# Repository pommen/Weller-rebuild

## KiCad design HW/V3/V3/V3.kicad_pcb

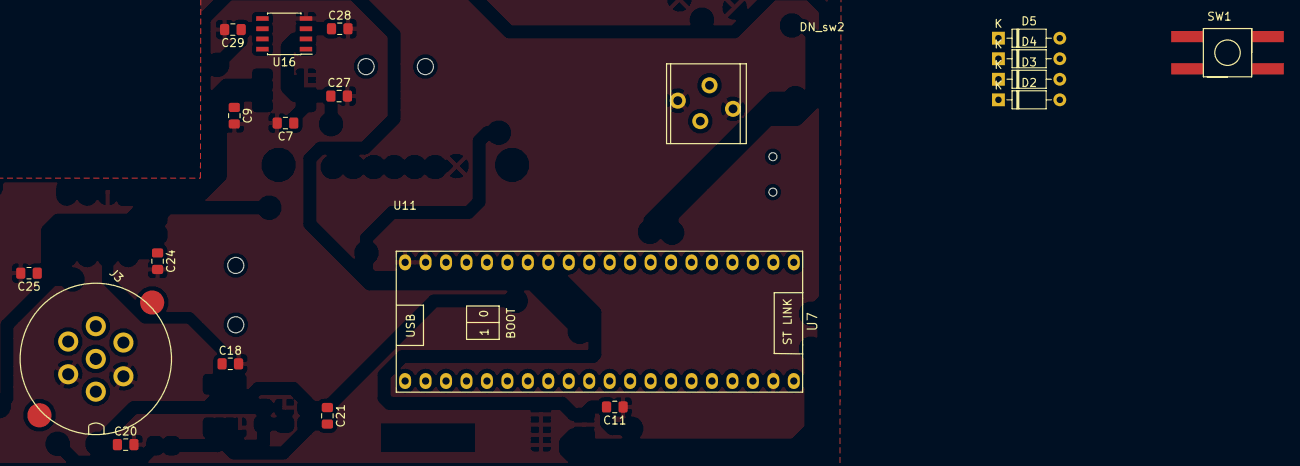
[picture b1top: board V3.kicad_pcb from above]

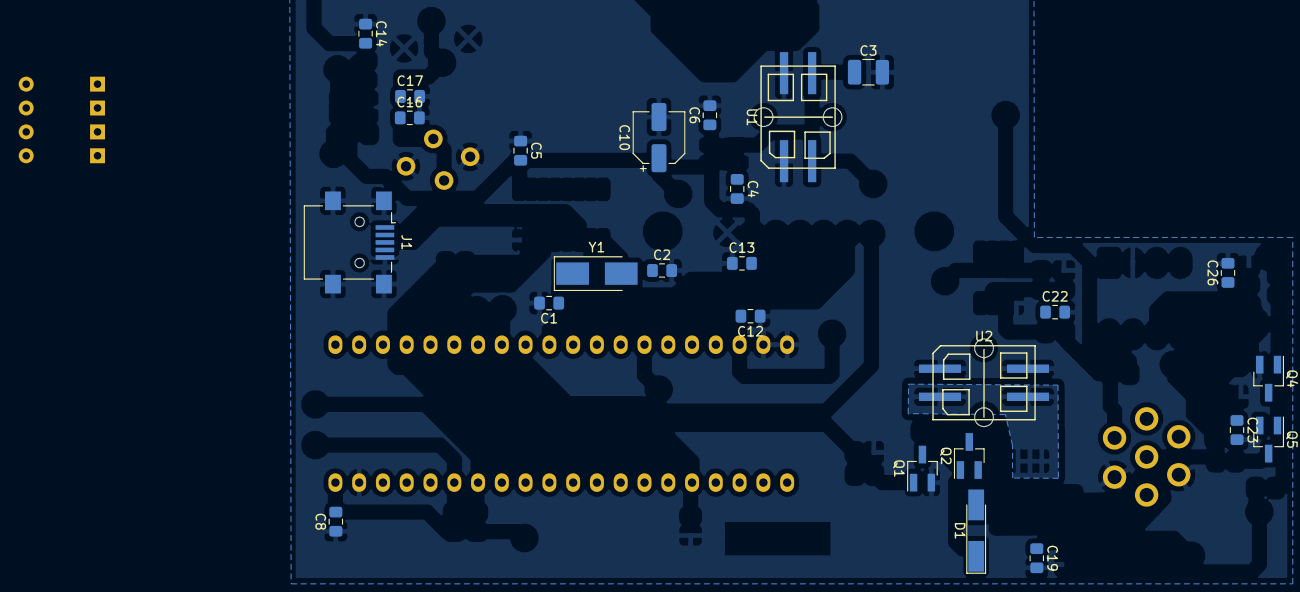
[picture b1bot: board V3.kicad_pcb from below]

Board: 2 copper layers, 47 parts (26 on the bottom side), 17 nets, no tracks yet.

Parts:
C1, C2: C_Small; C_0805_2012Metric_Pad1.15x1.40mm_HandSolder
C3: 68uf; C_1210_3225Metric_Pad1.42x2.65mm_HandSolder
C4: 1u; C_0805_2012Metric_Pad1.15x1.40mm_HandSolder
C5, C7, C8, C9, C11, C12, C13, C14, C18, C19, C20, C25: 100n; C_0805_2012Metric_Pad1.15x1.40mm_HandSolder
C6: 100pf; C_0805_2012Metric_Pad1.15x1.40mm_HandSolder
C10: 10uF; CP_Elec_5x5.3
C16, C17, C22, C23, C24, C26: 10n; C_0805_2012Metric_Pad1.15x1.40mm_HandSolder
C21: 1n; C_0805_2012Metric_Pad1.15x1.40mm_HandSolder
C27, C28, C29: 2.2uF; C_0805_2012Metric_Pad1.15x1.40mm_HandSolder
D1: 1N4148; D_MiniMELF_Handsoldering
D2, D3, D4, D5: 1N4148; D_DO-35_SOD27_P7.62mm_Horizontal
DN_sw2: SW_Push_Dual; WellerBTN
J1: USB_B_Mini; USB_Mini-B_Lumberg_2486_01_Horizontal
J3: WellerConn
Q1, Q2, Q4: BSS138; SOT-23_Handsoldering
Q5: A03401; SOT-23_Handsoldering
SW1: SW_Push; PushBTN KSC241G
U1: +7.5V; Conn_Microfit_Vertical_molex
U2: +24; Conn_Microfit_Vertical_molex
U7: Bluepill
U11: OLED_128x64_SPI_0.96; OLED_128x64_i2c
U16: MAX6241; SOIC-8_3.9x4.9mm_P1.27mm
Y1: 12MHZ; Crystal_SMD_5032-2Pin_5.0x3.2mm_HandSoldering

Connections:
+3V3: C5.2, C8.2, C10.1, C11.2, C12.2, C13.2, C14.2, U7.18, U7.40
+4V: C29.1, U16.6
+5V: C9.1, C18.1, C20.1, C25.1, D2.1, D4.1, Q5.2
+7.5V: C3.1, C4.1, C27.1, U1.2, U1.3, U16.2
+24V: Q2.3, U2.2, U2.3
/MOSFETCurr: C21.1, U7.14
GND: C1.2, C2.2, C3.2, C4.2, C5.1, C6.2, C7.2, C8.1, C9.2, C10.2, C11.1, C12.1, C13.1, C14.1, C16.2, C17.2, C18.2, C19.2, C20.2, C22.2, C23.2, C24.2, C25.2, C26.2, C27.2, C28.2, C29.2, D3.2, D5.2, DN_sw2.2, DN_sw2.4, J1.5, J1.6, J3.1, J3.5, Q1.2, Q4.2, SW1.2, U1.1, U1.4, U2.1, U2.4, U7.19, U7.20, U7.39, U16.4
unnamed: C1.1, Y1.1
unnamed: C2.1, Y1.2
unnamed: C16.1, DN_sw2.1, DN_sw2.3
unnamed: C22.1, D2.2, D3.1
unnamed: C23.1, D4.2, D5.1
unnamed: C28.1, U16.3
unnamed: D1.1, Q1.3, Q2.1
unnamed: D1.2, Q2.2
unnamed: Q4.3, Q5.1
unnamed: SW1.1, U7.17

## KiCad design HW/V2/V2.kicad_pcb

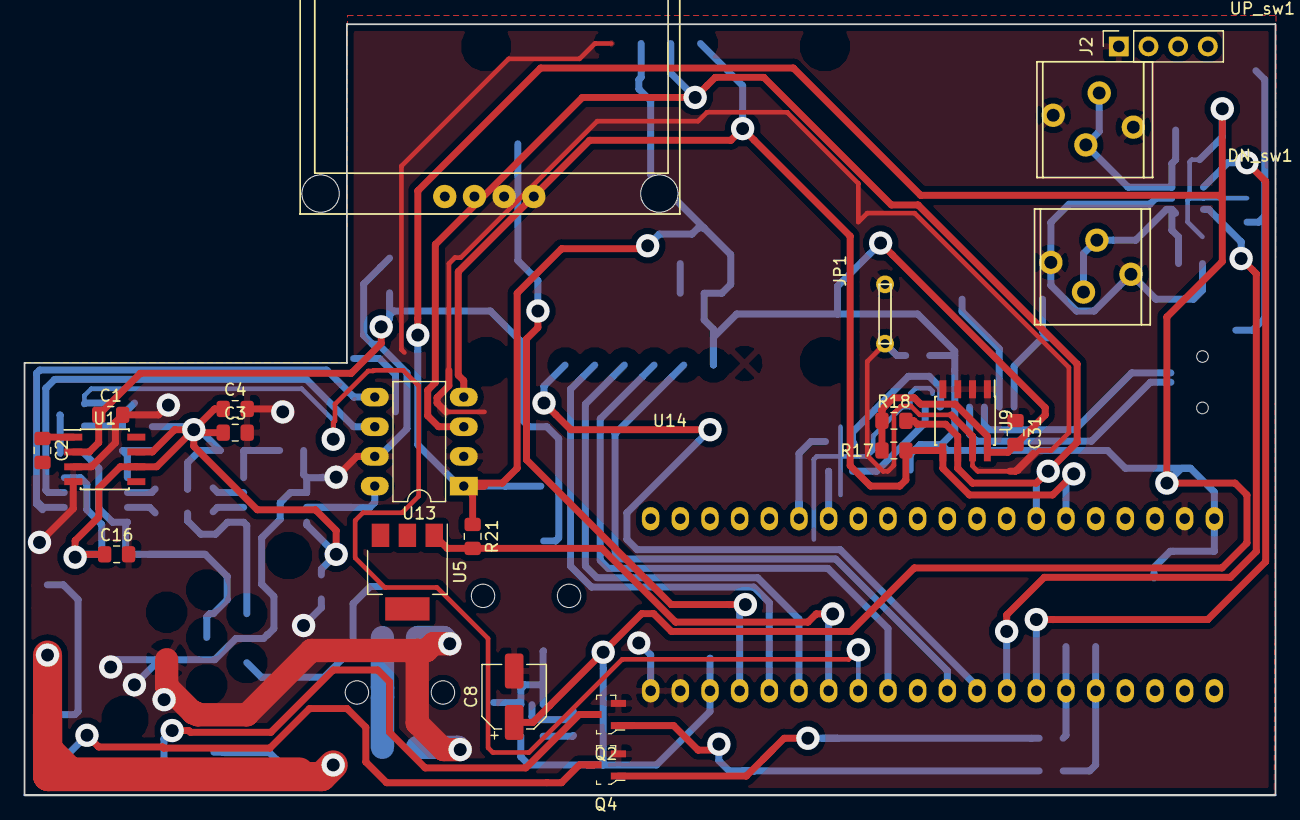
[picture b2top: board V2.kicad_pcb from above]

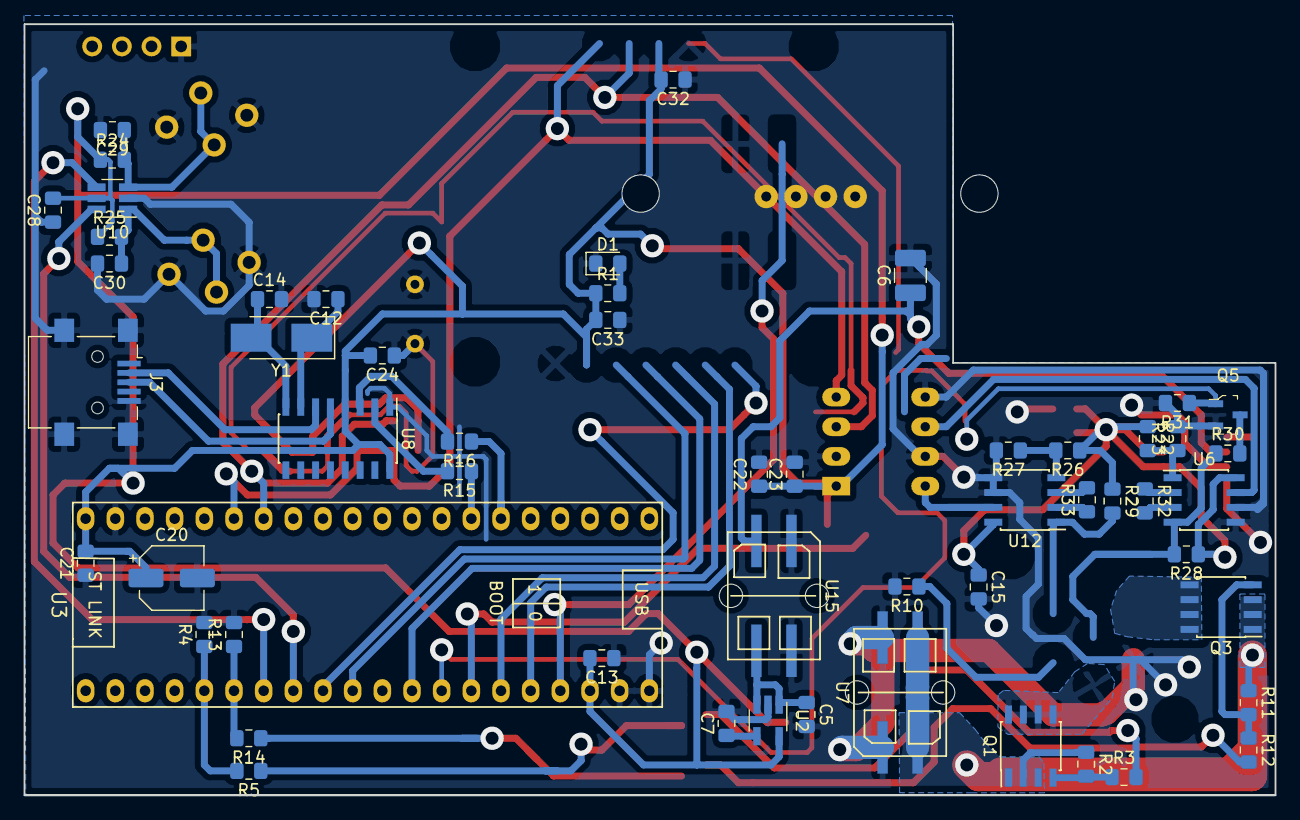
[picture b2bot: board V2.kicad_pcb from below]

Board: 2 copper layers, 107.1 x 66.0 mm, 76 parts (55 on the bottom side), 46 nets.

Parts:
C1, C2, C3: 100N; C_0805_2012Metric_Pad1.15x1.40mm_HandSolder
C4: 1u; C_0805_2012Metric_Pad1.15x1.40mm_HandSolder
C5: 1uF; C_0805_2012Metric_Pad1.15x1.40mm_HandSolder
C6: 68uf; C_1210_3225Metric_Pad1.42x2.65mm_HandSolder
C7: 100pF; C_0805_2012Metric_Pad1.15x1.40mm_HandSolder
C8: 2.2uF; CP_Elec_5x5.3
C12, C14: C_Small; C_0805_2012Metric_Pad1.15x1.40mm_HandSolder
C13, C15, C16, C21, C22, C24, C28, C31, C32, C33: 100n; C_0805_2012Metric_Pad1.15x1.40mm_HandSolder
C20: 10uF; CP_Elec_5x5.3
C23, C29, C30: 10n; C_0805_2012Metric_Pad1.15x1.40mm_HandSolder
D1: Green; D_0805_2012Metric_Pad1.15x1.40mm_HandSolder
DN_sw1: SW_Push_Dual; WellerBTN
J2: I2CHeader; PinSocket_1x04_P2.54mm_Vertical
J3: USB_B_Mini; USB_Mini-B_Lumberg_2486_01_Horizontal
JP1: Grounding pad; JUMPER_5MM
Q1, Q3: Si4435; SOIC-8_3.9x4.9mm_P1.27mm
Q2, Q4, Q5: BSS138; SOT-23-3
R1, R2, R3, R11, R12, R31: 10K; R_0805_2012Metric_Pad1.15x1.40mm_HandSolder
R4, R13, R24, R25: 100K; R_0805_2012Metric_Pad1.15x1.40mm_HandSolder
R5, R14: 100R; R_0805_2012Metric_Pad1.15x1.40mm_HandSolder
R10: 1M; R_0805_2012Metric_Pad1.15x1.40mm_HandSolder
R15, R16: 1k; R_0805_2012Metric_Pad1.15x1.40mm_HandSolder
R17, R18: 5k1; R_0805_2012Metric_Pad1.15x1.40mm_HandSolder
R21: 1K5-5K; R_0805_2012Metric_Pad1.15x1.40mm_HandSolder
R22, R23, R26, R27, R28, R29: 1K; R_0805_2012Metric_Pad1.15x1.40mm_HandSolder
R30: 2K; R_0805_2012Metric_Pad1.15x1.40mm_HandSolder
R32, R33: 5.62K 1%; R_0805_2012Metric_Pad1.15x1.40mm_HandSolder
U1: MAX6126_50; SOIC-8_3.9x4.9mm_P1.27mm
U2: AP2210-3.3V; SOT-23-5_HandSoldering
U3: Bluepill
U5: DS2401Z; SOT-223
U6, U12: AD8221; SOIC-8_3.9x4.9mm_P1.27mm
U7: +24VDC; Conn_Microfit_Vertical_molex
U8: CH340G; SOIC-16_3.9x9.9mm_P1.27mm
U9: M24C01-WMN; SOIC-8_3.9x4.9mm_P1.27mm
U10: 74HCT2G14GV; SOT-23-6_Handsoldering
U13: ADS1115-DIP; DIP-8_W7.62mm_LongPads
U14: OLED_128x64_SPI_0.96; OLED_128x64_i2c
U15: +7.5VDC; Conn_Microfit_Vertical_molex
UP_sw1: SW_Push_Dual; WellerBTN
Y1: 12MHZ; Crystal_SMD_5032-2Pin_5.0x3.2mm_HandSoldering

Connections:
+3V3: C8.1, C13.2, C20.1, C21.2, C22.1, C23.1, C24.2, C28.2, C31.2, C32.2, C33.2, J2.4, R1.1, R17.1, R18.1, R21.1, R24.1, R25.1, U2.5, U3.18, U3.40, U8.4, U8.16, U9.8, U10.5, U13.1, U14.2
+5vREF: C3.1, C4.1, C15.1, C16.1, R22.1, R26.1, R28.1, R29.1, U1.6, U1.7, U6.8, U12.8
+7.5V: C1.1, C5.1, C6.1, U1.2, U2.1, U2.3, U15.2, U15.3
+24V: Q1.1, Q1.2, Q1.3, Q3.1, Q3.2, Q3.3, R2.1, R11.1, U7.2, U7.3
/MCU/MOSFETtemp: R21.2, U3.14
/MCU/SCL: R18.2, U3.34, U9.6, U13.3, U14.3
/MCU/SDA: J2.2, J2.3, R17.2, U3.35, U9.5, U13.4, U14.4
/MCU/SolderPWM1: R4.1, R5.2, U3.5
/MCU/SolderPWM2: R13.1, R14.2, U3.6
/MCU/WMRTresistorDivider: Q5.1, R31.1, U3.13
BTN_DN: U3.7, U10.4
BTN_UP: U3.8, U10.6
GND: C1.2, C2.2, C3.2, C4.2, C5.2, C6.2, C7.2, C8.2, C12.2, C13.1, C14.2, C15.2, C16.2, C20.2, C21.1, C22.2, C23.2, C24.1, C28.1, C29.2, C30.2, C31.1, C32.1, C33.1, D1.1, DN_sw1.2, DN_sw1.4, J2.1, J3.5, J3.6, JP1.1, JP1.2, Q2.2, Q4.2, Q5.2, R4.2, R10.2, R13.2, R23.2, R27.2, R31.2, U1.3, U1.4, U2.2, U3.19, U3.20, U3.39, U6.5, U6.6, U7.1, U7.4, U8.1, U9.1, U9.2, U9.3, U9.4, U9.7, U10.2, U12.5, U12.6, U13.2, U13.5, U13.7, U14.1, U15.1, U15.4, UP_sw1.2, UP_sw1.4
HandleTempRaw: R29.2, U12.1
Heater1: Q1.5, Q1.6, Q1.7, Q1.8
Heater2: Q3.5, Q3.6, Q3.7, Q3.8
unnamed: C2.1, U1.1
unnamed: C7.1, U2.4
unnamed: C12.1, U8.7, Y1.1
unnamed: C14.1, U8.8, Y1.2
unnamed: C29.1, R24.2, U10.3, UP_sw1.1, UP_sw1.3
unnamed: C30.1, DN_sw1.1, DN_sw1.3, R25.2, U10.1
unnamed: D1.2, R1.2
unnamed: J3.2, U8.6
unnamed: J3.3, U8.5
unnamed: Q1.4, R2.2, R3.1
unnamed: Q2.1, R5.1
unnamed: Q2.3, R3.2
unnamed: Q3.4, R11.2, R12.1
unnamed: Q4.1, R14.1
unnamed: Q4.3, R12.2
unnamed: Q5.3, R30.2
unnamed: R15.1, U3.27
unnamed: R15.2, U8.2
unnamed: R16.1, U3.26
unnamed: R16.2, U8.3
unnamed: R32.1, U6.2
unnamed: R32.2, U6.3
unnamed: R33.1, U12.2
unnamed: R33.2, U12.3
unnamed: U5.2, U5.4
unnamed: U12.7, U13.8
unnamed: U6.7, U13.6
TC1+: R28.2, R30.1, U6.4
TC1-: R22.2, R23.1, U6.1
TC2-: R26.2, R27.1, U12.4

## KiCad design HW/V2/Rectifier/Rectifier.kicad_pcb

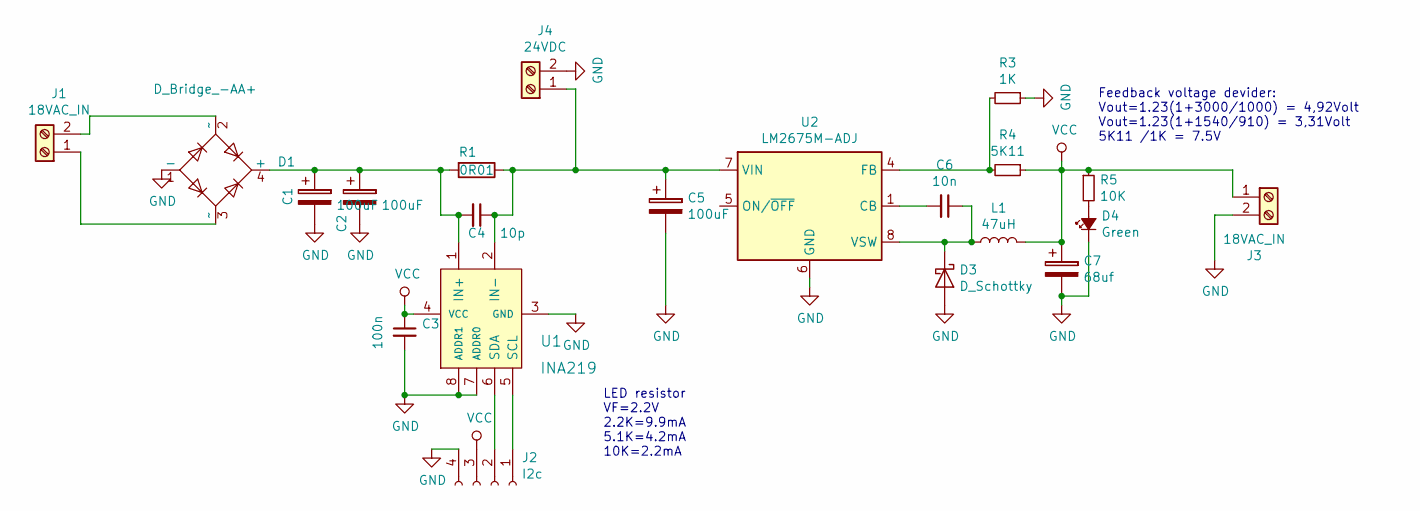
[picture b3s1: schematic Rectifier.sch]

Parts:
C1: 100uF; CP_Radial_D16.0mm_P7.50mm
C2: 100uF; CP_Elec_10x12.5
C3: 100n; C_0805_2012Metric_Pad1.15x1.40mm_HandSolder
C4: 10p; C_0805_2012Metric_Pad1.15x1.40mm_HandSolder
C5: 100uF; C_0805_2012Metric_Pad1.15x1.40mm_HandSolder
C6: 10n; C_0805_2012Metric_Pad1.15x1.40mm_HandSolder
C7: 68uf; CP_Elec_6.3x5.4
D1: D_Bridge_-AA+; RBU407
D3: D_Schottky; D_SMB_Handsoldering
D4: Green; D_0805_2012Metric_Pad1.15x1.40mm_HandSolder
J1, J3: 18VAC_IN; TerminalBlock_4Ucon_1x02_P3.50mm_Horizontal
J2: I2c; PinHeader_1x04_P2.54mm_Vertical
J4: 24VDC; TerminalBlock_4Ucon_1x02_P3.50mm_Horizontal
L1: 47uH; L_Neosid_SM-NE127_HandSoldering
R1: 0R01; R_2512_6332Metric_Pad1.52x3.35mm_HandSolder
R3: 1K; R_0805_2012Metric_Pad1.15x1.40mm_HandSolder
R4: 5K11; R_0805_2012Metric_Pad1.15x1.40mm_HandSolder
R5: 10K; R_0805_2012Metric_Pad1.15x1.40mm_HandSolder
U1: INA219; TSOT-23-8_HandSoldering
U2: LM2675M-ADJ; SOIC-8_3.9x4.9mm_P1.27mm

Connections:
GND: C1.2, C2.2, C3.2, C5.2, C7.2, D1.1 (-), D3.2 (A), D4.1 (K), J2.4, J3.2, J4.2, R3.1, U1.3 (GND), U1.7 (ADDR0), U1.8 (ADDR1), U2.6 (GND)
unnamed: C1.1, C2.1, C4.2, D1.4 (+), R1.2, U1.1 (IN+)
unnamed: C4.1, C5.1, J4.1, R1.1, U1.2 (IN-), U2.7 (VIN)
unnamed: C6.1, D3.1 (K), L1.1, U2.8 (VSW)
unnamed: C6.2, U2.1 (CB)
unnamed: D1.2 (~~), J1.2
unnamed: D1.3 (~~), J1.1
unnamed: D4.2 (A), R5.2
unnamed: J2.1, U1.5 (SCL)
unnamed: J2.2, U1.6 (SDA)
unnamed: R3.2, R4.2, U2.4 (FB)
VCC: C3.1, C7.1, J2.3, J3.1, L1.2, R4.1, R5.1, U1.4 (VCC)

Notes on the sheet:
Feedback voltage devider: Vout=1.23(1+3000/1000) = 4,92Volt Vout=1.23(1+1540/910) = 3,31Volt 5K11 /1K = 7.5V
LED resistor VF=2.2V 2.2K=9.9mA 5.1K=4.2mA 10K=2.2mA

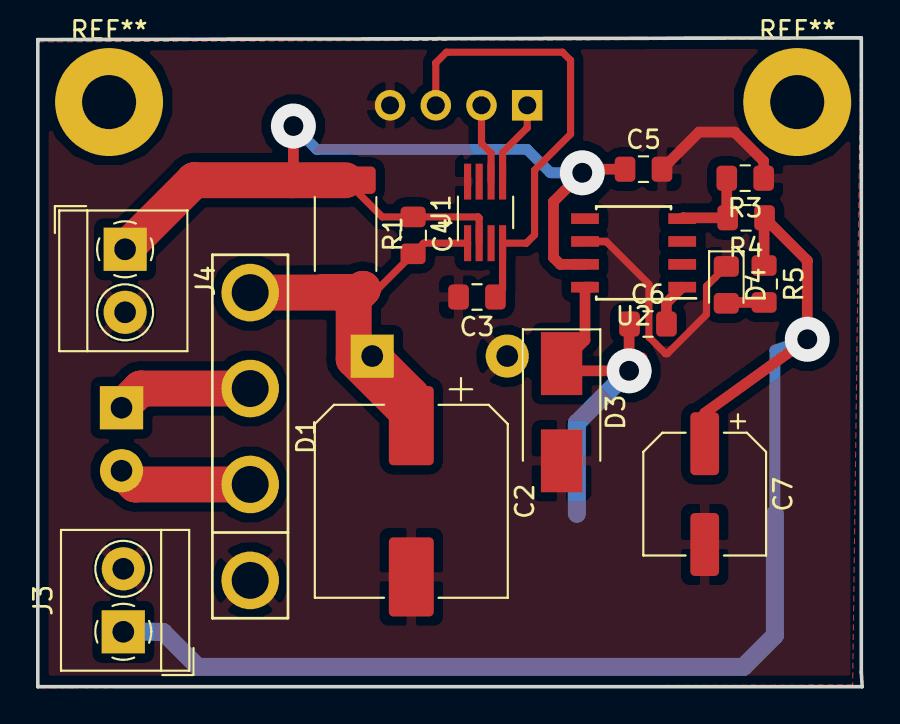
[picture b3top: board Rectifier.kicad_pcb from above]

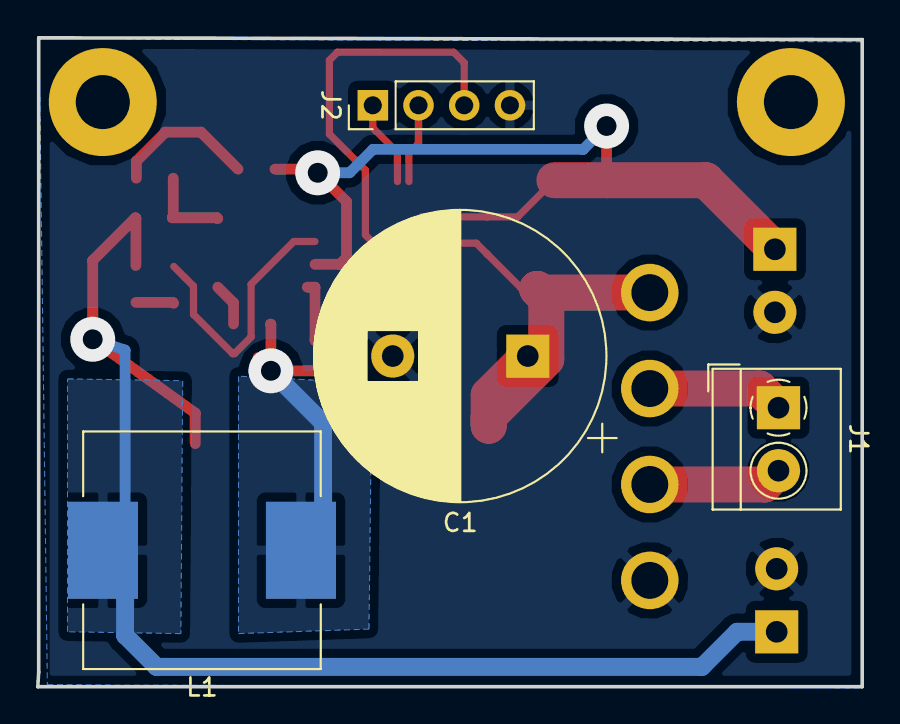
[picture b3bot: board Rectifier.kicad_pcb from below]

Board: 2 copper layers, 45.8 x 36.1 mm, 21 parts (4 on the bottom side), 12 nets.

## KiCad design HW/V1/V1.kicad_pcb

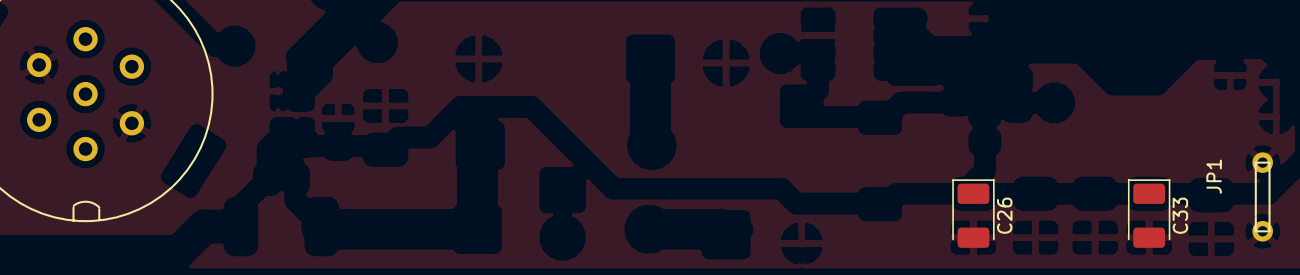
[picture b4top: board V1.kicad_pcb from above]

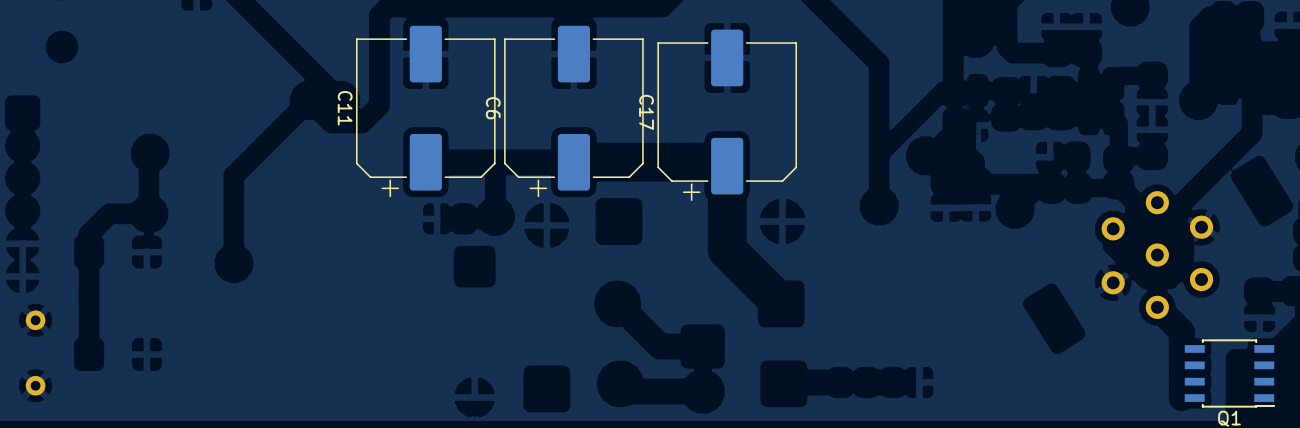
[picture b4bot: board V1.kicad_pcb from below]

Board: 2 copper layers, 9 parts (4 on the bottom side), 5 nets, no tracks yet.

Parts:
C6, C11, C17: 100uF; CP_Elec_10x10.5
C26, C33: 15u; CP_EIA-3528-15_AVX-H_Pad1.50x2.35mm_HandSolder
J3: WellerConn
JP1: Jumper; JUMPER_5MM
Q1: Si4435; SOIC-8_3.9x4.9mm_P1.27mm
U2: OLED_128x64_i2c_0.96; libOLED_128x64_i2c

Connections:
+24V: C6.1, C11.1, C17.1
GND: C6.2, C11.2, C17.2, C26.2, C33.2, J3.3, J3.7, JP1.1, JP1.2
unnamed: Q1.1, Q1.2, Q1.3
PWMtoTip: J3.2, Q1.5, Q1.6, Q1.7, Q1.8
VCC: C26.1, C33.1

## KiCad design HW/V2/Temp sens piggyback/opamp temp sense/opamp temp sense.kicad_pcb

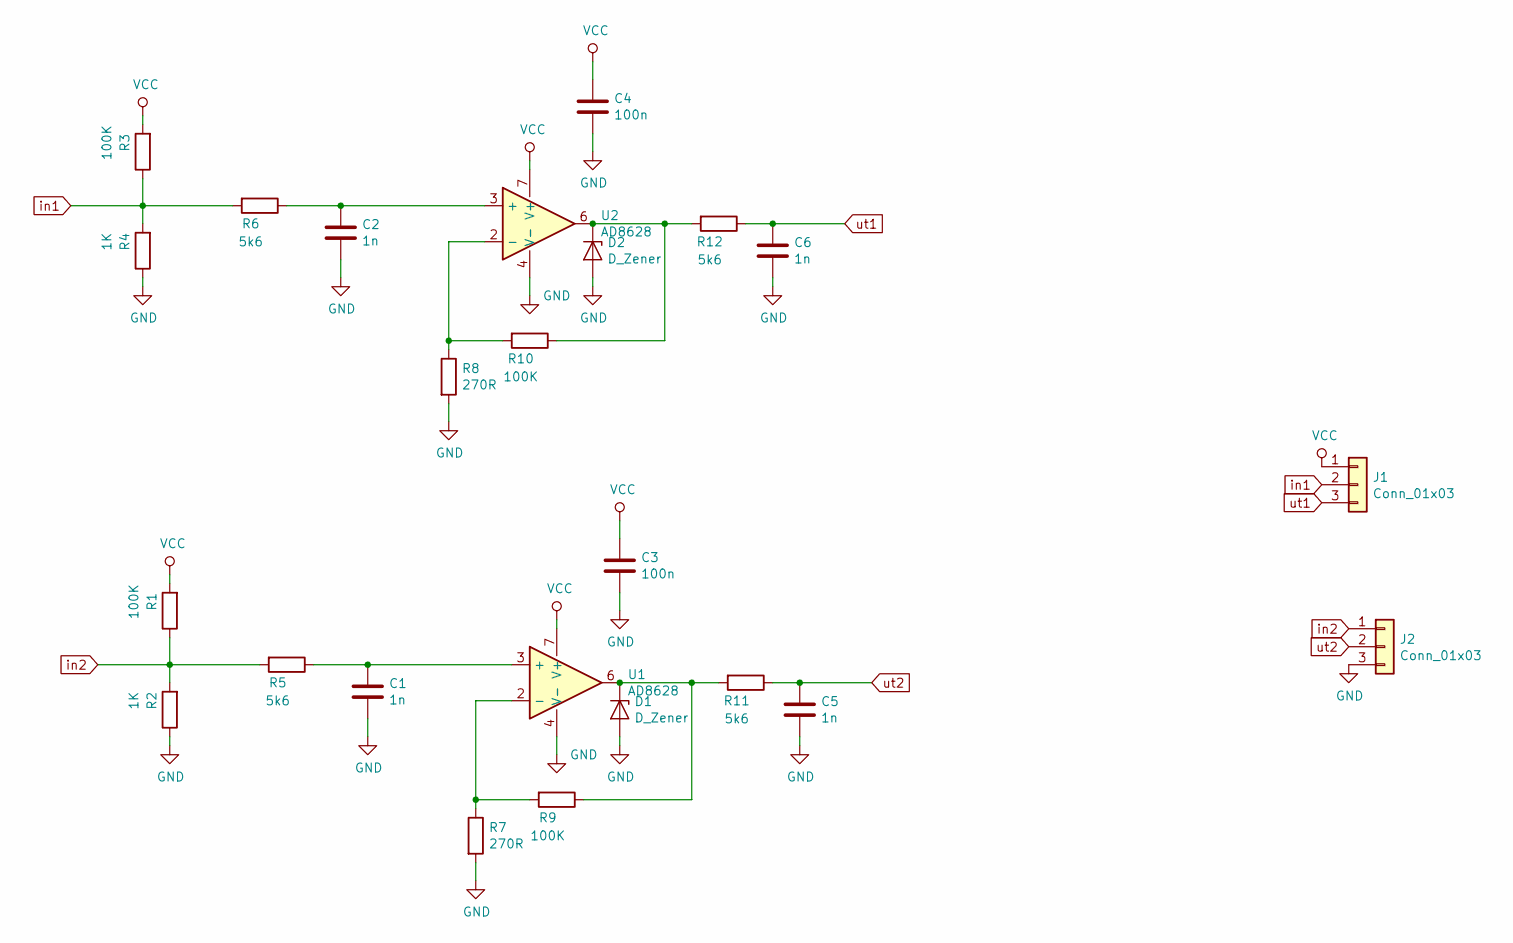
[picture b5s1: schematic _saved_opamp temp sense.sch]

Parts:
C1, C2, C5, C6: 1n; C_0805_2012Metric_Pad1.15x1.40mm_HandSolder
C3, C4: 100n; C_0805_2012Metric_Pad1.15x1.40mm_HandSolder
D1, D2: D_Zener; D_DO-15_P10.16mm_Horizontal
J1, J2: Conn_01x03; PinSocket_1x03_P2.54mm_Vertical
R1, R3, R9, R10: 100K; R_0805_2012Metric_Pad1.15x1.40mm_HandSolder
R2, R4: 1K; R_0805_2012Metric_Pad1.15x1.40mm_HandSolder
R5, R6, R11, R12: 5k6; R_0805_2012Metric_Pad1.15x1.40mm_HandSolder
R7, R8: 270R; R_0805_2012Metric_Pad1.15x1.40mm_HandSolder
U1, U2: AD8628; SOIC-8_3.9x4.9mm_P1.27mm

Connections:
GND: C1.2, C2.2, C3.2, C4.2, C5.2, C6.2, D1.2 (A), D2.2 (A), J2.3, R2.1, R4.1, R7.2, R8.2, U1.4 (V-), U2.4 (V-)
unnamed: C1.1, R5.1, U1.3 (+)
unnamed: C2.1, R6.1, U2.3 (+)
unnamed: D1.1 (K), R9.1, R11.2, U1.6
unnamed: D2.1 (K), R10.1, R12.2, U2.6
unnamed: R7.1, R9.2, U1.2 (-)
unnamed: R8.1, R10.2, U2.2 (-)
VCC: C3.1, C4.1, J1.1, R1.2, R3.2, U1.7 (V+), U2.7 (V+)
in1: J1.2, R3.1, R4.2, R6.2
in2: J2.1, R1.1, R2.2, R5.2
ut1: C6.1, J1.3, R12.1
ut2: C5.1, J2.2, R11.1

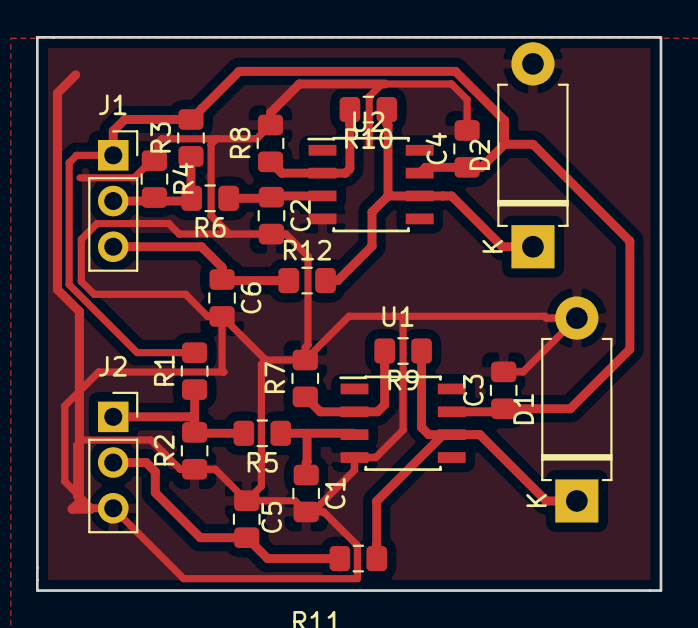
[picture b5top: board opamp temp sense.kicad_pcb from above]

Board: 2 copper layers, 34.6 x 30.7 mm, 24 parts (0 on the bottom side), 12 nets.

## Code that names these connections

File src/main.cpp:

#include <Arduino.h>
#include <U8g2lib.h>
#include <Wire.h>
#include <Adafruit_ADS1015.h>
#include <PID_v1.h>
#include <ArduinoSort.h>

//Pins:
const unsigned int heater1 = PA0;
const unsigned int heater2 = PA1;
const unsigned int BTN_UP = PA3;
const unsigned int BTN_DN = PA2;

//Protos:
//Temperature conversions
void pidAndPWM();
void setpoint();
int ADCRaw(int channel);
//Globals:
//Define the aggressive and conservative Tuning Parameters
float Setpoint, InputHeater1, InputHeater2, OutputHeater1, OutputHeater2;
float aggKp = 4, aggKi = 0.2, aggKd = 1;
float consKp = 1, consKi = 0.05, consKd = 0.25;

//Timers:
long unsigned int pidTimer = 0;

//Flags:

boolean notip1 = 0;
U8G2_SH1106_128X64_NONAME_F_HW_I2C u8g2(U8G2_R0, /* reset=*/U8X8_PIN_NONE);
Adafruit_ADS1115 ads; /* Use this for the 16-bit version */
PID PIDHeater1(&InputHeater1, &OutputHeater2, &Setpoint, consKp, consKi, consKd, DIRECT);
PID PIDHeater2(&InputHeater2, &OutputHeater2, &Setpoint, consKp, consKi, consKd, DIRECT);

#include <Temperature.h>
void setup(void)
{
	pinMode(heater1, OUTPUT);
	pinMode(heater2, OUTPUT);
	pinMode(BTN_DN, INPUT);
	pinMode(BTN_UP, INPUT);
	Serial.begin(9600);
	Wire.begin();
	//ads.setGain(GAIN_TWOTHIRDS); // 2/3x gain +/- 6.144V  1 bit = 3mV      0.1875mV (default)
	ads.setGain(GAIN_ONE); // 1x gain   +/- 4.096V  1 bit = 2mV      0.125mV
	// ads.setGain(GAIN_TWO);        // 2x gain   +/- 2.048V  1 bit = 1mV      0.0625mV
	//ads.setGain(GAIN_FOUR); // 4x gain   +/- 1.024V  1 bit = 0.5mV    0.03125mV
	// ads.setGain(GAIN_EIGHT);      // 8x gain   +/- 0.512V  1 bit = 0.25mV   0.015625mV
	// ads.setGain(GAIN_SIXTEEN);    // 16x gain  +/- 0.256V  1 bit = 0.125mV  0.0078125mV

	ads.begin();
	//analogWriteResolution()
	PIDHeater1.SetMode(AUTOMATIC);
	//myPID.SetInput
	//myPID.SetOutputLimits(0,65535);
	pidTimer = millis();

	tempSetup();

	while (1)
	{
		getTemp();
		Serial.print("HAndle: ");

		Serial.println((float)temperature_grip / 1000, 3);
		Serial.println();
		delay(1000);
	}

	Serial.println("Setup Done!");
}

void loop(void)
{
}

void pidAndPWM()
{
	InputHeater1 = getTemp();

	//no tip = no pid!
	if (InputHeater1 == 0)
	{
		OutputHeater1 = 0;
		OutputHeater2 = 0;
		return;
	}

	int gap = abs(Setpoint - InputHeater1); //distance away from setpoint
	if (gap < 50)
	{ //we're close to setpoint, use conservative tuning parameters
		PIDHeater1.SetTunings(consKp, consKi, consKd);
	}
	else
	{
		//we're far from setpoint, use aggressive tuning parameters
		PIDHeater1.SetTunings(aggKp, aggKi, aggKd);
	}

	PIDHeater1.Compute();
	analogWrite(heater1, OutputHeater1);
}

void setpoint()
{
}

void display()
{
}

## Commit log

2019-02-03 First commit
    First board is done
2019-02-03 Fized bugs
2019-02-09 V1 done
2019-02-10 V2 schematic
2019-02-11 V2 milling and BOM
2019-02-15 piggyback ADC amp
2019-02-17 handle Temp working
2019-02-27 iBOM
